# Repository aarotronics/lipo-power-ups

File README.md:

# Lipo Power UPS

DC uninterruptible power supply specially designed for 3D printers. It can be used in both 24V and 12V systems. 
For the recovery battery use a high capacity LiPo or LiIon battery, 6S for 24V and 3S for 12V. High power 
diodes conmutate power from power supply or battery so printer will no turn off even when electrical lines 
goes down. While 3D Printer is powering from power supply, current from battery will be 0A because of diode 
barrier, so it wont be discharged at all.

The time that system can keep the 3D Printer working with battery depends directly on how much power the 3D Printer 
drains itself; and also on the battery size, bigger battery will keep the system working for more time.

LiPo and LiIon batteries will damage if they get down of about 3V per cell, thats why the system has an integrated 
power MOSFET and a voltage sensing circuit that will turn off power from battery if it goes down the security 
voltage of 3V per cell. You may have to print again, but battery will be safe.

# Configuration

System can be used both for 24V and 12V systems. In case you are using 12V system, you will not have to use Q4, D17, 
R6 and C8 components. These components make a basic discrete 12V regulator to get 12V from a 24V system.

For 12V system you will have to close the jumper JP1, but for 24V leave it open!!

For 12V R1 should be 33K and for 24V R1 should be 75K. Make sure you are using precise resistor!! These resistors 
make part of the voltage sensor and measurement will be affected by these resistors.

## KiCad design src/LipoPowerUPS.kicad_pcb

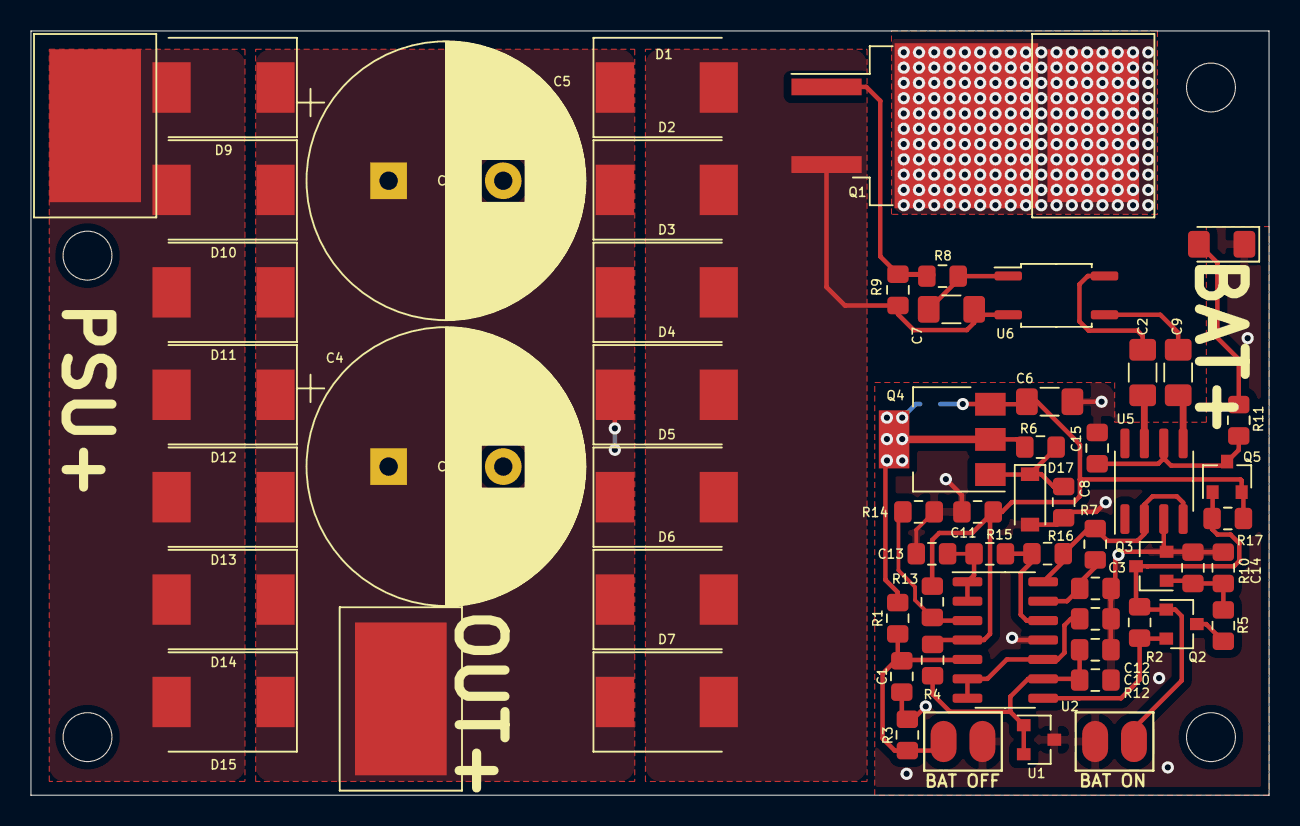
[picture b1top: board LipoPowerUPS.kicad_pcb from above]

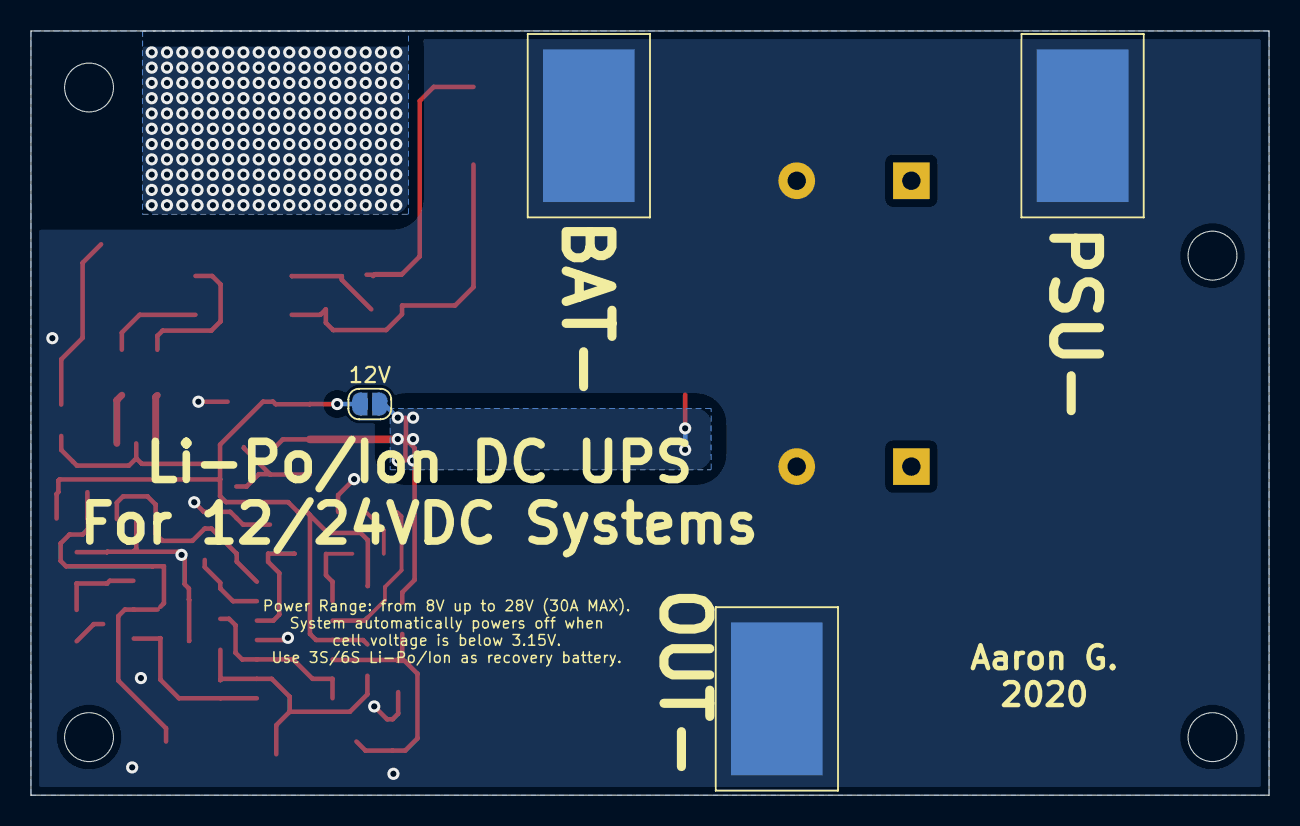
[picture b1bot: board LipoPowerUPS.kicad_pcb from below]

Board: 2 copper layers, 81.0 x 50.0 mm, 66 parts (4 on the bottom side), 27 nets.

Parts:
C1, C10, C12, C13, C14: 1u; C_0805_2012Metric_Pad1.15x1.40mm_HandSolder
C2, C6, C7, C9: 10u; C_1206_3216Metric_Pad1.42x1.75mm_HandSolder
C3, C8, C11, C15: 100n; C_0805_2012Metric_Pad1.15x1.40mm_HandSolder
C4, C5: 4700u; CP_Radial_D18.0mm_P7.50mm
D1, D2, D3, D4, D5, D6, D7, D9, D10, D11, D12, D13, D14, D15: SS54; D_SMC
D8: BAT ACTIVE; LED_1206_3216Metric_Pad1.42x1.75mm_HandSolder
D17: 12V; D_SOD-123
J1, J2: Battery; AGH_POWER_SMD_PAD
J3, J4: PowerSupply; AGH_POWER_SMD_PAD
J5, J6: OUT; AGH_POWER_SMD_PAD
JP1: 12V; SolderJumper-2_P1.3mm_Open_RoundedPad1.0x1.5mm
Q1: HY4008; TO-263-2
Q2, Q5: AO3401; SOT-23
Q3: AO3400; SOT-23
Q4: BCP56; SOT-223
R1: 120K/51K; R_0805_2012Metric_Pad1.15x1.40mm_HandSolder
R2, R10, R17: 470K; R_0805_2012Metric_Pad1.15x1.40mm_HandSolder
R3: 18K; R_0805_2012Metric_Pad1.15x1.40mm_HandSolder
R4: 3K3; R_0805_2012Metric_Pad1.15x1.40mm_HandSolder
R5: 22K; R_0805_2012Metric_Pad1.15x1.40mm_HandSolder
R6: 680; R_0805_2012Metric_Pad1.15x1.40mm_HandSolder
R7, R16: 2K2; R_0805_2012Metric_Pad1.15x1.40mm_HandSolder
R8: 100; R_0805_2012Metric_Pad1.15x1.40mm_HandSolder
R9: 330K; R_0805_2012Metric_Pad1.15x1.40mm_HandSolder
R11, R15: 1K; R_0805_2012Metric_Pad1.15x1.40mm_HandSolder
R12: 820K; R_0805_2012Metric_Pad1.15x1.40mm_HandSolder
R13, R14: 100K; R_0805_2012Metric_Pad1.15x1.40mm_HandSolder
SW1: BAT ON; AGH_CONN_1X02_2.54mm_SMD
SW2: BAT OFF; AGH_CONN_1X02_2.54mm_SMD
U1: TL431DBZ; SOT-23
U2: LM324; SOIC-14_3.9x8.7mm_P1.27mm
U5: MIC4428; SOIC-8_3.9x4.9mm_P1.27mm
U6: MB1S; SO-4_4.4x3.9mm_P2.54mm

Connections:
+12V: C6.1, C11.1, JP1.2, Q4.3, Q5.2, R4.2, R13.1, R17.1, U2.4
+24V: D9.2, D10.2, D11.2, D12.2, D13.2, D14.2, D15.2, J3.1
+BATT: J1.1, Q1.2
/2V5_REF: C10.1, R4.1, R12.2, U1.1, U1.2, U2.9
/CP1: C2.2, U5.7
/CP2: C9.2, U5.5
/GATE_VCC: C15.2, Q5.3, R11.1, U5.6
/MOSFET_G: Q1.1, R8.1, R9.1
/MOSFET_S: C7.2, D1.2, D2.2, D3.2, D4.2, D5.2, D6.2, D7.2, Q1.3, R9.2, U6.2
GND: C1.2, C3.1, C4.2, C5.2, C6.2, C8.2, C10.2, C11.2, C12.2, C13.1, C14.2, C15.1, D8.1, D17.2, J2.1, J4.1, J6.1, Q3.2, R3.2, R10.1, R12.1, R14.2, SW1.1, SW2.2, U1.3, U2.11, U5.3
unnamed: C1.1, R1.2, R3.1, SW2.1, U2.5
unnamed: C2.1, U6.4
unnamed: C3.2, R7.1, U2.13
unnamed: C7.1, R8.2, U6.1
unnamed: C8.1, D17.1, Q4.1, R6.1
unnamed: C9.1, U6.3
unnamed: C12.1, U2.6, U2.7, U2.10
unnamed: C13.2, R15.2, U2.1, U2.2
unnamed: C14.1, Q3.1, R5.1, R10.2
unnamed: D8.2, R11.2
unnamed: Q2.1, Q3.3, Q5.1, R2.2, R17.2, SW1.2
unnamed: Q2.2, R2.1, U2.8
unnamed: Q2.3, R5.2
unnamed: R13.2, R14.1, U2.3
unnamed: R15.1, R16.2, U2.12
unnamed: R7.2, R16.1, U2.14, U5.2, U5.4
VCC: C4.1, C5.1, D1.1, D2.1, D3.1, D4.1, D5.1, D6.1, D7.1, D9.1, D10.1, D11.1, D12.1, D13.1, D14.1, D15.1, J5.1, JP1.1, Q4.2, Q4.4, R1.1, R6.2

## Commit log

2020-03-02 Added files to repo
2020-11-15 Upload version V2.0
